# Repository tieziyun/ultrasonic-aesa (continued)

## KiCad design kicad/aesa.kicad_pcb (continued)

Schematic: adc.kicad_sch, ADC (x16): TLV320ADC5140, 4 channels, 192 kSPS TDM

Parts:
C1, C2, C3, C4, C5, C6, C7, C8, C10, C12, C14, C16: 100n 16V X7R; C_0603_1608Metric; LCSC C14663
C9, C17: 1u 50V X7R; C_0805_2012Metric; LCSC C28323
C11, C13, C15: 10u 16V X5R; C_0805_2012Metric; LCSC C15850
R1, R2, R3, R4: 2k 1%; R_0603_1608Metric; LCSC C22975
R5, R6, R7, R8: 1k 1%; R_0603_1608Metric; LCSC C21190
R9: 33 1%; R_0603_1608Metric; LCSC C23140
U1: TLV320ADC5140; Texas_RTW_WQFN-24-1EP_4x4mm_P0.5mm_EP2.7x2.7mm_ThermalVias; LCSC C2876368

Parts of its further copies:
C7101, C7102, C7103, C7104, C7105, C7106, C7107, C7108, C7110, C7112, C7114, C7116, C7201, C7202, C7203, C7204, C7205, C7206, C7207, C7208, C7210, C7212, C7214, C7216, C7301, C7302, C7303, C7304, C7305, C7306, C7307, C7308, C7310, C7312, C7314, C7316, C7401, C7402, C7403, C7404, C7405, C7406, C7407, C7408, C7410, C7412, C7414, C7416, C7501, C7502, C7503, C7504, C7505, C7506, C7507, C7508, C7510, C7512, C7514, C7516, C7601, C7602, C7603, C7604, C7605, C7606, C7607, C7608, C7610, C7612, C7614, C7616, C7701, C7702, C7703, C7704, C7705, C7706, C7707, C7708, C7710, C7712, C7714, C7716, C7801, C7802, C7803, C7804, C7805, C7806, C7807, C7808, C7810, C7812, C7814, C7816, C7901, C7902, C7903, C7904, C7905, C7906, C7907, C7908, C7910, C7912, C7914, C7916, C8001, C8002, C8003, C8004, C8005, C8006, C8007, C8008, C8010, C8012, C8014, C8016, C8101, C8102, C8103, C8104, C8105, C8106, C8107, C8108, C8110, C8112, C8114, C8116, C8201, C8202, C8203, C8204, C8205, C8206, C8207, C8208, C8210, C8212, C8214, C8216, C8301, C8302, C8303, C8304, C8305, C8306, C8307, C8308, C8310, C8312, C8314, C8316, C8401, C8402, C8403, C8404, C8405, C8406, C8407, C8408, C8410, C8412, C8414, C8416, C8501, C8502, C8503, C8504, C8505, C8506, C8507, C8508, C8510, C8512, C8514, C8516, C8601, C8602, C8603, C8604, C8605, C8606, C8607, C8608, C8610, C8612, C8614, C8616: 100n 16V X7R; C_0603_1608Metric; LCSC C14663
C7109, C7117, C7209, C7217, C7309, C7317, C7409, C7417, C7509, C7517, C7609, C7617, C7709, C7717, C7809, C7817, C7909, C7917, C8009, C8017, C8109, C8117, C8209, C8217, C8309, C8317, C8409, C8417, C8509, C8517, C8609, C8617: 1u 50V X7R; C_0805_2012Metric; LCSC C28323
C7111, C7113, C7115, C7211, C7213, C7215, C7311, C7313, C7315, C7411, C7413, C7415, C7511, C7513, C7515, C7611, C7613, C7615, C7711, C7713, C7715, C7811, C7813, C7815, C7911, C7913, C7915, C8011, C8013, C8015, C8111, C8113, C8115, C8211, C8213, C8215, C8311, C8313, C8315, C8411, C8413, C8415, C8511, C8513, C8515, C8611, C8613, C8615: 10u 16V X5R; C_0805_2012Metric; LCSC C15850
R7101, R7102, R7103, R7104, R7201, R7202, R7203, R7204, R7301, R7302, R7303, R7304, R7401, R7402, R7403, R7404, R7501, R7502, R7503, R7504, R7601, R7602, R7603, R7604, R7701, R7702, R7703, R7704, R7801, R7802, R7803, R7804, R7901, R7902, R7903, R7904, R8001, R8002, R8003, R8004, R8101, R8102, R8103, R8104, R8201, R8202, R8203, R8204, R8301, R8302, R8303, R8304, R8401, R8402, R8403, R8404, R8501, R8502, R8503, R8504, R8601, R8602, R8603, R8604: 2k 1%; R_0603_1608Metric; LCSC C22975
R7105, R7106, R7107, R7108, R7205, R7206, R7207, R7208, R7305, R7306, R7307, R7308, R7405, R7406, R7407, R7408, R7505, R7506, R7507, R7508, R7605, R7606, R7607, R7608, R7705, R7706, R7707, R7708, R7805, R7806, R7807, R7808, R7905, R7906, R7907, R7908, R8005, R8006, R8007, R8008, R8105, R8106, R8107, R8108, R8205, R8206, R8207, R8208, R8305, R8306, R8307, R8308, R8405, R8406, R8407, R8408, R8505, R8506, R8507, R8508, R8605, R8606, R8607, R8608: 1k 1%; R_0603_1608Metric; LCSC C21190
R7109, R7209, R7309, R7409, R7509, R7609, R7709, R7809, R7909, R8009, R8109, R8209, R8309, R8409, R8509, R8609: 33 1%; R_0603_1608Metric; LCSC C23140
U7101, U7201, U7301, U7401, U7501, U7601, U7701, U7801, U7901, U8001, U8101, U8201, U8301, U8401, U8501, U8601: TLV320ADC5140; Texas_RTW_WQFN-24-1EP_4x4mm_P0.5mm_EP2.7x2.7mm_ThermalVias; LCSC C2876368

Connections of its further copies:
+3V3: C7115.1, C7116.1, C7215.1, C7216.1, C7315.1, C7316.1, C7415.1, C7416.1, C7515.1, C7516.1, C7615.1, C7616.1, C7715.1, C7716.1, C7815.1, C7816.1, C7915.1, C7916.1, C8015.1, C8016.1, C8115.1, C8116.1, C8215.1, C8216.1, C8315.1, C8316.1, C8415.1, C8416.1, C8515.1, C8516.1, C8615.1, C8616.1, U7101.19 (IOVDD), U7201.16 (ADDR0_SCLK), U7201.19 (IOVDD), U7301.15 (ADDR1_MISO), U7301.19 (IOVDD), U7401.15 (ADDR1_MISO), U7401.16 (ADDR0_SCLK), U7401.19 (IOVDD), U7501.19 (IOVDD), U7601.16 (ADDR0_SCLK), U7601.19 (IOVDD), U7701.15 (ADDR1_MISO), U7701.19 (IOVDD), U7801.15 (ADDR1_MISO), U7801.16 (ADDR0_SCLK), U7801.19 (IOVDD), U7901.19 (IOVDD), U8001.16 (ADDR0_SCLK), U8001.19 (IOVDD), U8101.15 (ADDR1_MISO), U8101.19 (IOVDD), U8201.15 (ADDR1_MISO), U8201.16 (ADDR0_SCLK), U8201.19 (IOVDD), U8301.19 (IOVDD), U8401.16 (ADDR0_SCLK), U8401.19 (IOVDD), U8501.15 (ADDR1_MISO), U8501.19 (IOVDD), U8601.15 (ADDR1_MISO), U8601.16 (ADDR0_SCLK), U8601.19 (IOVDD); also elsewhere on the board
+3V3A: C7109.1, C7110.1, C7209.1, C7210.1, C7309.1, C7310.1, C7409.1, C7410.1, C7509.1, C7510.1, C7609.1, C7610.1, C7709.1, C7710.1, C7809.1, C7810.1, C7909.1, C7910.1, C8009.1, C8010.1, C8109.1, C8110.1, C8209.1, C8210.1, C8309.1, C8310.1, C8409.1, C8410.1, C8509.1, C8510.1, C8609.1, C8610.1, U7101.1 (AVDD), U7201.1 (AVDD), U7301.1 (AVDD), U7401.1 (AVDD), U7501.1 (AVDD), U7601.1 (AVDD), U7701.1 (AVDD), U7801.1 (AVDD), U7901.1 (AVDD), U8001.1 (AVDD), U8101.1 (AVDD), U8201.1 (AVDD), U8301.1 (AVDD), U8401.1 (AVDD), U8501.1 (AVDD), U8601.1 (AVDD); also elsewhere on the board
/ADCs/ADC01/AREG: C7111.1, C7112.1, U7101.2 (AREG)
/ADCs/ADC01/DREG: C7113.1, C7114.1, U7101.24 (DREG)
/ADCs/ADC01/INM1: C7105.1, U7101.7 (IN1M_GPO1)
/ADCs/ADC01/INM2: C7106.1, U7101.9 (IN2M_GPO2)
/ADCs/ADC01/INM3: C7107.1, U7101.11 (IN3M_GPO3)
/ADCs/ADC01/INM4: C7108.1, U7101.13 (IN4M_GPO4)
/ADCs/ADC01/INP1: C7101.2, U7101.6 (IN1P_GPI1)
/ADCs/ADC01/INP2: C7102.2, U7101.8 (IN2P_GPI2)
/ADCs/ADC01/INP3: C7103.2, U7101.10 (IN3P_GPI3)
/ADCs/ADC01/INP4: C7104.2, U7101.12 (IN4P_GPI4)
/ADCs/ADC01/VREF: C7117.1, U7101.3 (VREF)
/ADCs/ADC02/AREG: C7211.1, C7212.1, U7201.2 (AREG)
/ADCs/ADC02/DREG: C7213.1, C7214.1, U7201.24 (DREG)
/ADCs/ADC02/INM1: C7205.1, U7201.7 (IN1M_GPO1)
/ADCs/ADC02/INM2: C7206.1, U7201.9 (IN2M_GPO2)
/ADCs/ADC02/INM3: C7207.1, U7201.11 (IN3M_GPO3)
/ADCs/ADC02/INM4: C7208.1, U7201.13 (IN4M_GPO4)
/ADCs/ADC02/INP1: C7201.2, U7201.6 (IN1P_GPI1)
/ADCs/ADC02/INP2: C7202.2, U7201.8 (IN2P_GPI2)
/ADCs/ADC02/INP3: C7203.2, U7201.10 (IN3P_GPI3)
/ADCs/ADC02/INP4: C7204.2, U7201.12 (IN4P_GPI4)
/ADCs/ADC02/VREF: C7217.1, U7201.3 (VREF)
/ADCs/ADC03/AREG: C7311.1, C7312.1, U7301.2 (AREG)
/ADCs/ADC03/DREG: C7313.1, C7314.1, U7301.24 (DREG)
/ADCs/ADC03/INM1: C7305.1, U7301.7 (IN1M_GPO1)
/ADCs/ADC03/INM2: C7306.1, U7301.9 (IN2M_GPO2)
/ADCs/ADC03/INM3: C7307.1, U7301.11 (IN3M_GPO3)
/ADCs/ADC03/INM4: C7308.1, U7301.13 (IN4M_GPO4)
/ADCs/ADC03/INP1: C7301.2, U7301.6 (IN1P_GPI1)
/ADCs/ADC03/INP2: C7302.2, U7301.8 (IN2P_GPI2)
/ADCs/ADC03/INP3: C7303.2, U7301.10 (IN3P_GPI3)
/ADCs/ADC03/INP4: C7304.2, U7301.12 (IN4P_GPI4)
/ADCs/ADC03/VREF: C7317.1, U7301.3 (VREF)
/ADCs/ADC04/AREG: C7411.1, C7412.1, U7401.2 (AREG)
/ADCs/ADC04/DREG: C7413.1, C7414.1, U7401.24 (DREG)
/ADCs/ADC04/INM1: C7405.1, U7401.7 (IN1M_GPO1)
/ADCs/ADC04/INM2: C7406.1, U7401.9 (IN2M_GPO2)
/ADCs/ADC04/INM3: C7407.1, U7401.11 (IN3M_GPO3)
/ADCs/ADC04/INM4: C7408.1, U7401.13 (IN4M_GPO4)
/ADCs/ADC04/INP1: C7401.2, U7401.6 (IN1P_GPI1)
/ADCs/ADC04/INP2: C7402.2, U7401.8 (IN2P_GPI2)
/ADCs/ADC04/INP3: C7403.2, U7401.10 (IN3P_GPI3)
/ADCs/ADC04/INP4: C7404.2, U7401.12 (IN4P_GPI4)
/ADCs/ADC04/VREF: C7417.1, U7401.3 (VREF)
/ADCs/ADC05/AREG: C7511.1, C7512.1, U7501.2 (AREG)
/ADCs/ADC05/DREG: C7513.1, C7514.1, U7501.24 (DREG)
/ADCs/ADC05/INM1: C7505.1, U7501.7 (IN1M_GPO1)
/ADCs/ADC05/INM2: C7506.1, U7501.9 (IN2M_GPO2)
/ADCs/ADC05/INM3: C7507.1, U7501.11 (IN3M_GPO3)
/ADCs/ADC05/INM4: C7508.1, U7501.13 (IN4M_GPO4)
/ADCs/ADC05/INP1: C7501.2, U7501.6 (IN1P_GPI1)
/ADCs/ADC05/INP2: C7502.2, U7501.8 (IN2P_GPI2)
/ADCs/ADC05/INP3: C7503.2, U7501.10 (IN3P_GPI3)
/ADCs/ADC05/INP4: C7504.2, U7501.12 (IN4P_GPI4)
/ADCs/ADC05/VREF: C7517.1, U7501.3 (VREF)
/ADCs/ADC06/AREG: C7611.1, C7612.1, U7601.2 (AREG)
/ADCs/ADC06/DREG: C7613.1, C7614.1, U7601.24 (DREG)
/ADCs/ADC06/INM1: C7605.1, U7601.7 (IN1M_GPO1)
/ADCs/ADC06/INM2: C7606.1, U7601.9 (IN2M_GPO2)
/ADCs/ADC06/INM3: C7607.1, U7601.11 (IN3M_GPO3)
/ADCs/ADC06/INM4: C7608.1, U7601.13 (IN4M_GPO4)
/ADCs/ADC06/INP1: C7601.2, U7601.6 (IN1P_GPI1)
/ADCs/ADC06/INP2: C7602.2, U7601.8 (IN2P_GPI2)
/ADCs/ADC06/INP3: C7603.2, U7601.10 (IN3P_GPI3)
/ADCs/ADC06/INP4: C7604.2, U7601.12 (IN4P_GPI4)
/ADCs/ADC06/VREF: C7617.1, U7601.3 (VREF)
/ADCs/ADC07/AREG: C7711.1, C7712.1, U7701.2 (AREG)
/ADCs/ADC07/DREG: C7713.1, C7714.1, U7701.24 (DREG)
/ADCs/ADC07/INM1: C7705.1, U7701.7 (IN1M_GPO1)
/ADCs/ADC07/INM2: C7706.1, U7701.9 (IN2M_GPO2)
/ADCs/ADC07/INM3: C7707.1, U7701.11 (IN3M_GPO3)
/ADCs/ADC07/INM4: C7708.1, U7701.13 (IN4M_GPO4)
/ADCs/ADC07/INP1: C7701.2, U7701.6 (IN1P_GPI1)
/ADCs/ADC07/INP2: C7702.2, U7701.8 (IN2P_GPI2)
/ADCs/ADC07/INP3: C7703.2, U7701.10 (IN3P_GPI3)
/ADCs/ADC07/INP4: C7704.2, U7701.12 (IN4P_GPI4)
/ADCs/ADC07/VREF: C7717.1, U7701.3 (VREF)
/ADCs/ADC08/AREG: C7811.1, C7812.1, U7801.2 (AREG)
/ADCs/ADC08/DREG: C7813.1, C7814.1, U7801.24 (DREG)
/ADCs/ADC08/INM1: C7805.1, U7801.7 (IN1M_GPO1)
/ADCs/ADC08/INM2: C7806.1, U7801.9 (IN2M_GPO2)
/ADCs/ADC08/INM3: C7807.1, U7801.11 (IN3M_GPO3)
/ADCs/ADC08/INM4: C7808.1, U7801.13 (IN4M_GPO4)
/ADCs/ADC08/INP1: C7801.2, U7801.6 (IN1P_GPI1)
/ADCs/ADC08/INP2: C7802.2, U7801.8 (IN2P_GPI2)
/ADCs/ADC08/INP3: C7803.2, U7801.10 (IN3P_GPI3)
/ADCs/ADC08/INP4: C7804.2, U7801.12 (IN4P_GPI4)
/ADCs/ADC08/VREF: C7817.1, U7801.3 (VREF)
/ADCs/ADC09/AREG: C7911.1, C7912.1, U7901.2 (AREG)
/ADCs/ADC09/DREG: C7913.1, C7914.1, U7901.24 (DREG)
/ADCs/ADC09/INM1: C7905.1, U7901.7 (IN1M_GPO1)
/ADCs/ADC09/INM2: C7906.1, U7901.9 (IN2M_GPO2)
/ADCs/ADC09/INM3: C7907.1, U7901.11 (IN3M_GPO3)
/ADCs/ADC09/INM4: C7908.1, U7901.13 (IN4M_GPO4)
/ADCs/ADC09/INP1: C7901.2, U7901.6 (IN1P_GPI1)
/ADCs/ADC09/INP2: C7902.2, U7901.8 (IN2P_GPI2)
/ADCs/ADC09/INP3: C7903.2, U7901.10 (IN3P_GPI3)
/ADCs/ADC09/INP4: C7904.2, U7901.12 (IN4P_GPI4)
/ADCs/ADC09/VREF: C7917.1, U7901.3 (VREF)
/ADCs/ADC10/AREG: C8011.1, C8012.1, U8001.2 (AREG)
/ADCs/ADC10/DREG: C8013.1, C8014.1, U8001.24 (DREG)
/ADCs/ADC10/INM1: C8005.1, U8001.7 (IN1M_GPO1)
/ADCs/ADC10/INM2: C8006.1, U8001.9 (IN2M_GPO2)
/ADCs/ADC10/INM3: C8007.1, U8001.11 (IN3M_GPO3)
/ADCs/ADC10/INM4: C8008.1, U8001.13 (IN4M_GPO4)
/ADCs/ADC10/INP1: C8001.2, U8001.6 (IN1P_GPI1)
/ADCs/ADC10/INP2: C8002.2, U8001.8 (IN2P_GPI2)
/ADCs/ADC10/INP3: C8003.2, U8001.10 (IN3P_GPI3)
/ADCs/ADC10/INP4: C8004.2, U8001.12 (IN4P_GPI4)
/ADCs/ADC10/VREF: C8017.1, U8001.3 (VREF)
/ADCs/ADC11/AREG: C8111.1, C8112.1, U8101.2 (AREG)
/ADCs/ADC11/DREG: C8113.1, C8114.1, U8101.24 (DREG)
/ADCs/ADC11/INM1: C8105.1, U8101.7 (IN1M_GPO1)
/ADCs/ADC11/INM2: C8106.1, U8101.9 (IN2M_GPO2)
/ADCs/ADC11/INM3: C8107.1, U8101.11 (IN3M_GPO3)
/ADCs/ADC11/INM4: C8108.1, U8101.13 (IN4M_GPO4)
/ADCs/ADC11/INP1: C8101.2, U8101.6 (IN1P_GPI1)
/ADCs/ADC11/INP2: C8102.2, U8101.8 (IN2P_GPI2)
/ADCs/ADC11/INP3: C8103.2, U8101.10 (IN3P_GPI3)
/ADCs/ADC11/INP4: C8104.2, U8101.12 (IN4P_GPI4)
/ADCs/ADC11/VREF: C8117.1, U8101.3 (VREF)
/ADCs/ADC12/AREG: C8211.1, C8212.1, U8201.2 (AREG)
/ADCs/ADC12/DREG: C8213.1, C8214.1, U8201.24 (DREG)
/ADCs/ADC12/INM1: C8205.1, U8201.7 (IN1M_GPO1)
/ADCs/ADC12/INM2: C8206.1, U8201.9 (IN2M_GPO2)
/ADCs/ADC12/INM3: C8207.1, U8201.11 (IN3M_GPO3)
/ADCs/ADC12/INM4: C8208.1, U8201.13 (IN4M_GPO4)
/ADCs/ADC12/INP1: C8201.2, U8201.6 (IN1P_GPI1)
/ADCs/ADC12/INP2: C8202.2, U8201.8 (IN2P_GPI2)
/ADCs/ADC12/INP3: C8203.2, U8201.10 (IN3P_GPI3)
/ADCs/ADC12/INP4: C8204.2, U8201.12 (IN4P_GPI4)
/ADCs/ADC12/VREF: C8217.1, U8201.3 (VREF)
/ADCs/ADC13/AREG: C8311.1, C8312.1, U8301.2 (AREG)
/ADCs/ADC13/DREG: C8313.1, C8314.1, U8301.24 (DREG)
/ADCs/ADC13/INM1: C8305.1, U8301.7 (IN1M_GPO1)
/ADCs/ADC13/INM2: C8306.1, U8301.9 (IN2M_GPO2)
/ADCs/ADC13/INM3: C8307.1, U8301.11 (IN3M_GPO3)
/ADCs/ADC13/INM4: C8308.1, U8301.13 (IN4M_GPO4)
/ADCs/ADC13/INP1: C8301.2, U8301.6 (IN1P_GPI1)
/ADCs/ADC13/INP2: C8302.2, U8301.8 (IN2P_GPI2)
/ADCs/ADC13/INP3: C8303.2, U8301.10 (IN3P_GPI3)
/ADCs/ADC13/INP4: C8304.2, U8301.12 (IN4P_GPI4)
/ADCs/ADC13/VREF: C8317.1, U8301.3 (VREF)
/ADCs/ADC14/AREG: C8411.1, C8412.1, U8401.2 (AREG)
/ADCs/ADC14/DREG: C8413.1, C8414.1, U8401.24 (DREG)
/ADCs/ADC14/INM1: C8405.1, U8401.7 (IN1M_GPO1)
/ADCs/ADC14/INM2: C8406.1, U8401.9 (IN2M_GPO2)
/ADCs/ADC14/INM3: C8407.1, U8401.11 (IN3M_GPO3)
/ADCs/ADC14/INM4: C8408.1, U8401.13 (IN4M_GPO4)
/ADCs/ADC14/INP1: C8401.2, U8401.6 (IN1P_GPI1)
/ADCs/ADC14/INP2: C8402.2, U8401.8 (IN2P_GPI2)
/ADCs/ADC14/INP3: C8403.2, U8401.10 (IN3P_GPI3)
/ADCs/ADC14/INP4: C8404.2, U8401.12 (IN4P_GPI4)
/ADCs/ADC14/VREF: C8417.1, U8401.3 (VREF)
/ADCs/ADC15/AREG: C8511.1, C8512.1, U8501.2 (AREG)
/ADCs/ADC15/DREG: C8513.1, C8514.1, U8501.24 (DREG)
/ADCs/ADC15/INM1: C8505.1, U8501.7 (IN1M_GPO1)
/ADCs/ADC15/INM2: C8506.1, U8501.9 (IN2M_GPO2)
/ADCs/ADC15/INM3: C8507.1, U8501.11 (IN3M_GPO3)
/ADCs/ADC15/INM4: C8508.1, U8501.13 (IN4M_GPO4)
/ADCs/ADC15/INP1: C8501.2, U8501.6 (IN1P_GPI1)
/ADCs/ADC15/INP2: C8502.2, U8501.8 (IN2P_GPI2)
/ADCs/ADC15/INP3: C8503.2, U8501.10 (IN3P_GPI3)
/ADCs/ADC15/INP4: C8504.2, U8501.12 (IN4P_GPI4)
/ADCs/ADC15/VREF: C8517.1, U8501.3 (VREF)
/ADCs/ADC16/AREG: C8611.1, C8612.1, U8601.2 (AREG)
/ADCs/ADC16/DREG: C8613.1, C8614.1, U8601.24 (DREG)
/ADCs/ADC16/INM1: C8605.1, U8601.7 (IN1M_GPO1)
/ADCs/ADC16/INM2: C8606.1, U8601.9 (IN2M_GPO2)
/ADCs/ADC16/INM3: C8607.1, U8601.11 (IN3M_GPO3)
/ADCs/ADC16/INM4: C8608.1, U8601.13 (IN4M_GPO4)
/ADCs/ADC16/INP1: C8601.2, U8601.6 (IN1P_GPI1)
/ADCs/ADC16/INP2: C8602.2, U8601.8 (IN2P_GPI2)
/ADCs/ADC16/INP3: C8603.2, U8601.10 (IN3P_GPI3)
/ADCs/ADC16/INP4: C8604.2, U8601.12 (IN4P_GPI4)
/ADCs/ADC16/VREF: C8617.1, U8601.3 (VREF)
ADC_BCLK_A: U7101.22 (BCLK), U7201.22 (BCLK), U7301.22 (BCLK), U7401.22 (BCLK); also elsewhere on the board
ADC_BCLK_B: U7501.22 (BCLK), U7601.22 (BCLK), U7701.22 (BCLK), U7801.22 (BCLK); also elsewhere on the board
ADC_BCLK_C: U7901.22 (BCLK), U8001.22 (BCLK), U8101.22 (BCLK), U8201.22 (BCLK); also elsewhere on the board
ADC_BCLK_D: U8301.22 (BCLK), U8401.22 (BCLK), U8501.22 (BCLK), U8601.22 (BCLK); also elsewhere on the board
ADC_FSYNC_A: U7101.23 (FSYNC), U7201.23 (FSYNC), U7301.23 (FSYNC), U7401.23 (FSYNC); also elsewhere on the board
ADC_FSYNC_B: U7501.23 (FSYNC), U7601.23 (FSYNC), U7701.23 (FSYNC), U7801.23 (FSYNC); also elsewhere on the board
ADC_FSYNC_C: U7901.23 (FSYNC), U8001.23 (FSYNC), U8101.23 (FSYNC), U8201.23 (FSYNC); also elsewhere on the board
ADC_FSYNC_D: U8301.23 (FSYNC), U8401.23 (FSYNC), U8501.23 (FSYNC), U8601.23 (FSYNC); also elsewhere on the board
ADC_SCL: U7101.17 (SCL_MOSI), U7201.17 (SCL_MOSI), U7301.17 (SCL_MOSI), U7401.17 (SCL_MOSI), U7501.17 (SCL_MOSI), U7601.17 (SCL_MOSI), U7701.17 (SCL_MOSI), U7801.17 (SCL_MOSI), U7901.17 (SCL_MOSI), U8001.17 (SCL_MOSI), U8101.17 (SCL_MOSI), U8201.17 (SCL_MOSI), U8301.17 (SCL_MOSI), U8401.17 (SCL_MOSI), U8501.17 (SCL_MOSI), U8601.17 (SCL_MOSI); also elsewhere on the board
ADC_SDA1: U7101.18 (SDA_SSZ), U7201.18 (SDA_SSZ), U7301.18 (SDA_SSZ), U7401.18 (SDA_SSZ); also elsewhere on the board
ADC_SDA2: U7501.18 (SDA_SSZ), U7601.18 (SDA_SSZ), U7701.18 (SDA_SSZ), U7801.18 (SDA_SSZ); also elsewhere on the board
ADC_SDA3: U7901.18 (SDA_SSZ), U8001.18 (SDA_SSZ), U8101.18 (SDA_SSZ), U8201.18 (SDA_SSZ); also elsewhere on the board
ADC_SDA4: U8301.18 (SDA_SSZ), U8401.18 (SDA_SSZ), U8501.18 (SDA_SSZ), U8601.18 (SDA_SSZ); also elsewhere on the board
ADC_SDOUT1: R7109.2; also elsewhere on the board
ADC_SDOUT2: R7209.2; also elsewhere on the board
ADC_SDOUT3: R7309.2; also elsewhere on the board
ADC_SDOUT4: R7409.2; also elsewhere on the board
ADC_SDOUT5: R7509.2; also elsewhere on the board
ADC_SDOUT6: R7609.2; also elsewhere on the board
ADC_SDOUT7: R7709.2; also elsewhere on the board
ADC_SDOUT8: R7809.2; also elsewhere on the board
ADC_SDOUT9: R7909.2; also elsewhere on the board
ADC_SDOUT10: R8009.2; also elsewhere on the board
ADC_SDOUT11: R8109.2; also elsewhere on the board
ADC_SDOUT12: R8209.2; also elsewhere on the board
ADC_SDOUT13: R8309.2; also elsewhere on the board
ADC_SDOUT14: R8409.2; also elsewhere on the board
ADC_SDOUT15: R8509.2; also elsewhere on the board
ADC_SDOUT16: R8609.2; also elsewhere on the board
ADC_SHDNZ: U7101.14 (SHDNZ), U7201.14 (SHDNZ), U7301.14 (SHDNZ), U7401.14 (SHDNZ), U7501.14 (SHDNZ), U7601.14 (SHDNZ), U7701.14 (SHDNZ), U7801.14 (SHDNZ), U7901.14 (SHDNZ), U8001.14 (SHDNZ), U8101.14 (SHDNZ), U8201.14 (SHDNZ), U8301.14 (SHDNZ), U8401.14 (SHDNZ), U8501.14 (SHDNZ), U8601.14 (SHDNZ); also elsewhere on the board
GND: C7105.2, C7106.2, C7107.2, C7108.2, C7109.2, C7110.2, C7111.2, C7112.2, C7113.2, C7114.2, C7115.2, C7116.2, C7117.2, C7205.2, C7206.2, C7207.2, C7208.2, C7209.2, C7210.2, C7211.2, C7212.2, C7213.2, C7214.2, C7215.2, C7216.2, C7217.2, C7305.2, C7306.2, C7307.2, C7308.2, C7309.2, C7310.2, C7311.2, C7312.2, C7313.2, C7314.2, C7315.2, C7316.2, C7317.2, C7405.2, C7406.2, C7407.2, C7408.2, C7409.2, C7410.2, C7411.2, C7412.2, C7413.2, C7414.2, C7415.2, C7416.2, C7417.2, C7505.2, C7506.2, C7507.2, C7508.2, C7509.2, C7510.2, C7511.2, C7512.2, C7513.2, C7514.2, C7515.2, C7516.2, C7517.2, C7605.2, C7606.2, C7607.2, C7608.2, C7609.2, C7610.2, C7611.2, C7612.2, C7613.2, C7614.2, C7615.2, C7616.2, C7617.2, C7705.2, C7706.2, C7707.2, C7708.2, C7709.2, C7710.2, C7711.2, C7712.2, C7713.2, C7714.2, C7715.2, C7716.2, C7717.2, C7805.2, C7806.2, C7807.2, C7808.2, C7809.2, C7810.2, C7811.2, C7812.2, C7813.2, C7814.2, C7815.2, C7816.2, C7817.2, C7905.2, C7906.2, C7907.2, C7908.2, C7909.2, C7910.2, C7911.2, C7912.2, C7913.2, C7914.2, C7915.2, C7916.2, C7917.2, C8005.2, C8006.2, C8007.2, C8008.2, C8009.2, C8010.2, C8011.2, C8012.2, C8013.2, C8014.2, C8015.2, C8016.2, C8017.2, C8105.2, C8106.2, C8107.2, C8108.2, C8109.2, C8110.2, C8111.2, C8112.2, C8113.2, C8114.2, C8115.2, C8116.2, C8117.2, C8205.2, C8206.2, C8207.2, C8208.2, C8209.2, C8210.2, C8211.2, C8212.2, C8213.2, C8214.2, C8215.2, C8216.2, C8217.2, C8305.2, C8306.2, C8307.2, C8308.2, C8309.2, C8310.2, C8311.2, C8312.2, C8313.2, C8314.2, C8315.2, C8316.2, C8317.2, C8405.2, C8406.2, C8407.2, C8408.2, C8409.2, C8410.2, C8411.2, C8412.2, C8413.2, C8414.2, C8415.2, C8416.2, C8417.2, C8505.2, C8506.2, C8507.2, C8508.2, C8509.2, C8510.2, C8511.2, C8512.2, C8513.2, C8514.2, C8515.2, C8516.2, C8517.2, C8605.2, C8606.2, C8607.2, C8608.2, C8609.2, C8610.2, C8611.2, C8612.2, C8613.2, C8614.2, C8615.2, C8616.2, C8617.2, R7105.2, R7106.2, R7107.2, R7108.2, R7205.2, R7206.2, R7207.2, R7208.2, R7305.2, R7306.2, R7307.2, R7308.2, R7405.2, R7406.2, R7407.2, R7408.2, R7505.2, R7506.2, R7507.2, R7508.2, R7605.2, R7606.2, R7607.2, R7608.2, R7705.2, R7706.2, R7707.2, R7708.2, R7805.2, R7806.2, R7807.2, R7808.2, R7905.2, R7906.2, R7907.2, R7908.2, R8005.2, R8006.2, R8007.2, R8008.2, R8105.2, R8106.2, R8107.2, R8108.2, R8205.2, R8206.2, R8207.2, R8208.2, R8305.2, R8306.2, R8307.2, R8308.2, R8405.2, R8406.2, R8407.2, R8408.2, R8505.2, R8506.2, R8507.2, R8508.2, R8605.2, R8606.2, R8607.2, R8608.2, U7101.4 (AVSS), U7101.15 (ADDR1_MISO), U7101.16 (ADDR0_SCLK), U7101.25 (VSS), U7201.4 (AVSS), U7201.15 (ADDR1_MISO), U7201.25 (VSS), U7301.4 (AVSS), U7301.16 (ADDR0_SCLK), U7301.25 (VSS), U7401.4 (AVSS), U7401.25 (VSS), U7501.4 (AVSS), U7501.15 (ADDR1_MISO), U7501.16 (ADDR0_SCLK), U7501.25 (VSS), U7601.4 (AVSS), U7601.15 (ADDR1_MISO), U7601.25 (VSS), U7701.4 (AVSS), U7701.16 (ADDR0_SCLK), U7701.25 (VSS), U7801.4 (AVSS), U7801.25 (VSS), U7901.4 (AVSS), U7901.15 (ADDR1_MISO), U7901.16 (ADDR0_SCLK), U7901.25 (VSS), U8001.4 (AVSS), U8001.15 (ADDR1_MISO), U8001.25 (VSS), U8101.4 (AVSS), U8101.16 (ADDR0_SCLK), U8101.25 (VSS), U8201.4 (AVSS), U8201.25 (VSS), U8301.4 (AVSS), U8301.15 (ADDR1_MISO), U8301.16 (ADDR0_SCLK), U8301.25 (VSS), U8401.4 (AVSS), U8401.15 (ADDR1_MISO), U8401.25 (VSS), U8501.4 (AVSS), U8501.16 (ADDR0_SCLK), U8501.25 (VSS), U8601.4 (AVSS), U8601.25 (VSS); also elsewhere on the board
unnamed: C7101.1, R7101.2, R7105.1
unnamed: C7102.1, R7102.2, R7106.1
unnamed: C7103.1, R7103.2, R7107.1
unnamed: C7104.1, R7104.2, R7108.1
unnamed: C7201.1, R7201.2, R7205.1
unnamed: C7202.1, R7202.2, R7206.1
unnamed: C7203.1, R7203.2, R7207.1
unnamed: C7204.1, R7204.2, R7208.1
unnamed: C7301.1, R7301.2, R7305.1
unnamed: C7302.1, R7302.2, R7306.1
unnamed: C7303.1, R7303.2, R7307.1
unnamed: C7304.1, R7304.2, R7308.1
unnamed: C7401.1, R7401.2, R7405.1
unnamed: C7402.1, R7402.2, R7406.1
unnamed: C7403.1, R7403.2, R7407.1
unnamed: C7404.1, R7404.2, R7408.1
unnamed: C7501.1, R7501.2, R7505.1
unnamed: C7502.1, R7502.2, R7506.1
unnamed: C7503.1, R7503.2, R7507.1
unnamed: C7504.1, R7504.2, R7508.1
unnamed: C7601.1, R7601.2, R7605.1
unnamed: C7602.1, R7602.2, R7606.1
unnamed: C7603.1, R7603.2, R7607.1
unnamed: C7604.1, R7604.2, R7608.1
unnamed: C7701.1, R7701.2, R7705.1
unnamed: C7702.1, R7702.2, R7706.1
unnamed: C7703.1, R7703.2, R7707.1
unnamed: C7704.1, R7704.2, R7708.1
unnamed: C7801.1, R7801.2, R7805.1
unnamed: C7802.1, R7802.2, R7806.1
unnamed: C7803.1, R7803.2, R7807.1
unnamed: C7804.1, R7804.2, R7808.1
unnamed: C7901.1, R7901.2, R7905.1
unnamed: C7902.1, R7902.2, R7906.1
unnamed: C7903.1, R7903.2, R7907.1
unnamed: C7904.1, R7904.2, R7908.1
unnamed: C8001.1, R8001.2, R8005.1
unnamed: C8002.1, R8002.2, R8006.1
unnamed: C8003.1, R8003.2, R8007.1
unnamed: C8004.1, R8004.2, R8008.1
unnamed: C8101.1, R8101.2, R8105.1
unnamed: C8102.1, R8102.2, R8106.1
unnamed: C8103.1, R8103.2, R8107.1
unnamed: C8104.1, R8104.2, R8108.1
unnamed: C8201.1, R8201.2, R8205.1
unnamed: C8202.1, R8202.2, R8206.1
unnamed: C8203.1, R8203.2, R8207.1
unnamed: C8204.1, R8204.2, R8208.1
unnamed: C8301.1, R8301.2, R8305.1
unnamed: C8302.1, R8302.2, R8306.1
unnamed: C8303.1, R8303.2, R8307.1
unnamed: C8304.1, R8304.2, R8308.1
unnamed: C8401.1, R8401.2, R8405.1
unnamed: C8402.1, R8402.2, R8406.1
unnamed: C8403.1, R8403.2, R8407.1
unnamed: C8404.1, R8404.2, R8408.1
unnamed: C8501.1, R8501.2, R8505.1
unnamed: C8502.1, R8502.2, R8506.1
unnamed: C8503.1, R8503.2, R8507.1
unnamed: C8504.1, R8504.2, R8508.1
unnamed: C8601.1, R8601.2, R8605.1
unnamed: C8602.1, R8602.2, R8606.1
unnamed: C8603.1, R8603.2, R8607.1
unnamed: C8604.1, R8604.2, R8608.1
unnamed: R7109.1, U7101.21 (SDOUT)
unnamed: R7209.1, U7201.21 (SDOUT)
unnamed: R7309.1, U7301.21 (SDOUT)
unnamed: R7409.1, U7401.21 (SDOUT)
unnamed: R7509.1, U7501.21 (SDOUT)
unnamed: R7609.1, U7601.21 (SDOUT)
unnamed: R7709.1, U7701.21 (SDOUT)
unnamed: R7809.1, U7801.21 (SDOUT)
unnamed: R7909.1, U7901.21 (SDOUT)
unnamed: R8009.1, U8001.21 (SDOUT)
unnamed: R8109.1, U8101.21 (SDOUT)
unnamed: R8209.1, U8201.21 (SDOUT)
unnamed: R8309.1, U8301.21 (SDOUT)
unnamed: R8409.1, U8401.21 (SDOUT)
unnamed: R8509.1, U8501.21 (SDOUT)
unnamed: R8609.1, U8601.21 (SDOUT)
RX1: R7104.1; also elsewhere on the board
RX2: R7103.1; also elsewhere on the board
RX3: R7102.1; also elsewhere on the board
RX4: R7101.1; also elsewhere on the board
RX5: R7204.1; also elsewhere on the board
RX6: R7203.1; also elsewhere on the board
RX7: R7202.1; also elsewhere on the board
RX8: R7201.1; also elsewhere on the board
RX9: R7304.1; also elsewhere on the board
RX10: R7303.1; also elsewhere on the board
RX11: R7302.1; also elsewhere on the board
RX12: R7301.1; also elsewhere on the board
RX13: R7404.1; also elsewhere on the board
RX14: R7403.1; also elsewhere on the board
RX15: R7402.1; also elsewhere on the board
RX16: R7401.1; also elsewhere on the board
RX17: R7504.1; also elsewhere on the board
RX18: R7503.1; also elsewhere on the board
RX19: R7502.1; also elsewhere on the board
RX20: R7501.1; also elsewhere on the board
RX21: R7604.1; also elsewhere on the board
RX22: R7603.1; also elsewhere on the board
RX23: R7602.1; also elsewhere on the board
RX24: R7601.1; also elsewhere on the board
RX25: R7704.1; also elsewhere on the board
RX26: R7703.1; also elsewhere on the board
RX27: R7702.1; also elsewhere on the board
RX28: R7701.1; also elsewhere on the board
RX29: R7804.1; also elsewhere on the board
RX30: R7803.1; also elsewhere on the board
RX31: R7802.1; also elsewhere on the board
RX32: R7801.1; also elsewhere on the board
RX33: R7904.1; also elsewhere on the board
RX34: R7903.1; also elsewhere on the board
RX35: R7902.1; also elsewhere on the board
RX36: R7901.1; also elsewhere on the board
RX37: R8004.1; also elsewhere on the board
RX38: R8003.1; also elsewhere on the board
RX39: R8002.1; also elsewhere on the board
RX40: R8001.1; also elsewhere on the board
RX41: R8104.1; also elsewhere on the board
RX42: R8103.1; also elsewhere on the board
RX43: R8102.1; also elsewhere on the board
RX44: R8101.1; also elsewhere on the board
RX45: R8204.1; also elsewhere on the board
RX46: R8203.1; also elsewhere on the board
RX47: R8202.1; also elsewhere on the board
RX48: R8201.1; also elsewhere on the board
RX49: R8304.1; also elsewhere on the board
RX50: R8303.1; also elsewhere on the board
RX51: R8302.1; also elsewhere on the board
RX52: R8301.1; also elsewhere on the board
RX53: R8404.1; also elsewhere on the board
RX54: R8403.1; also elsewhere on the board
RX55: R8402.1; also elsewhere on the board
RX56: R8401.1; also elsewhere on the board
RX57: R8504.1; also elsewhere on the board
RX58: R8503.1; also elsewhere on the board
RX59: R8502.1; also elsewhere on the board
RX60: R8501.1; also elsewhere on the board
RX61: R8604.1; also elsewhere on the board
RX62: R8603.1; also elsewhere on the board
RX63: R8602.1; also elsewhere on the board
RX64: R8601.1; also elsewhere on the board

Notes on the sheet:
Input: 2k/1k divider (x0.31 with the 10 k input) keeps the receiver's +-4.2 V worst case inside the 1.41 V peak full scale; 100 nF couples to the ADC's own bias (150 Hz high-pass).
Per channel, set at boot: CHx_INSRC = single-ended (01), CHx_IMP = 10 k (01), AC-coupled, fixed 0 dB gain, DRE and AGC OFF (they change gain on the fly and break channel matching).
ADC: TLV320ADC5140 (TI, 4 channels, up to 768 kSPS). Run at 192 kSPS: flat to about 86 kHz.
TDM slave: BCLK 18.432 MHz, FSYNC 192 kHz from the FPGA (shared by all 16 ADCs, so all 64 channels sample at the same instant). 4 slots x 24 bits on SDOUT.
Decoupling at the pins (datasheet Figure 172): AVDD 1 uF + 100 nF, AREG and DREG 10 uF + 100 nF, IOVDD 10 uF + 100 nF, VREF 1 uF
I2C: SCL shared, SDA per group of 4 ADCs; A1/A0 set the address 0x4C-0x4F inside the group. Config writes can use I2C broadcast (P0_R2 I2C_BRDCAST_EN).
Also: ADC_FSCALE 2.75 V (1 Vrms single-ended full scale), AREG_SELECT = 1, TX_EDGE = 1 (the FPGA latches SDOUT one BCLK after launch).
Ports IN1-IN4 are the block's four elements in order; IN1 feeds ADC channel 4 ... IN4 channel 1 (the order the receive lanes reach the inputs on the board). TDM: channel c carries element 4k-4 + (5 - c).
Channel inputs: 2k + 1k divider, 100 nF AC coupling (single-ended, INxM AC-grounded)
Power-up: SHDNZ (ADC_SHDNZ, pulled low on the header sheet) stays low until the rails settle, then wait 2 ms before I2C.

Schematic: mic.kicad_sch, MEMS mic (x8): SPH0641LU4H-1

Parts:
C1: 100n 50V C0G 1206; C_1206_3216Metric; LCSC C170182
MK1: SPH0641LU4H-1; Knowles_LGA-5_3.5x2.65mm; LCSC C2879853
R1: 33 1%; R_0603_1608Metric; LCSC C23140

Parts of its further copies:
C14101, C14201, C14301, C14401, C14501, C14601, C14701, C14801: 100n 50V C0G 1206; C_1206_3216Metric; LCSC C170182
MK14101, MK14201, MK14301, MK14401, MK14501, MK14601, MK14701, MK14801: SPH0641LU4H-1; Knowles_LGA-5_3.5x2.65mm; LCSC C2879853
R14101, R14201, R14301, R14401, R14501, R14601, R14701, R14801: 33 1%; R_0603_1608Metric; LCSC C23140

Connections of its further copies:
3V3_MIC: C14101.1, C14201.1, C14301.1, C14401.1, C14501.1, C14601.1, C14701.1, C14801.1, MK14101.2 (SEL), MK14101.5 (VDD), MK14201.5 (VDD), MK14301.2 (SEL), MK14301.5 (VDD), MK14401.5 (VDD), MK14501.2 (SEL), MK14501.5 (VDD), MK14601.5 (VDD), MK14701.2 (SEL), MK14701.5 (VDD), MK14801.5 (VDD); also elsewhere on the board
GND: C14101.2, C14201.2, C14301.2, C14401.2, C14501.2, C14601.2, C14701.2, C14801.2, MK14101.3 (GND), MK14201.2 (SEL), MK14201.3 (GND), MK14301.3 (GND), MK14401.2 (SEL), MK14401.3 (GND), MK14501.3 (GND), MK14601.2 (SEL), MK14601.3 (GND), MK14701.3 (GND), MK14801.2 (SEL), MK14801.3 (GND); also elsewhere on the board
MIC_CLK_A: MK14101.4 (CLOCK), MK14201.4 (CLOCK); also elsewhere on the board
MIC_CLK_B: MK14301.4 (CLOCK), MK14401.4 (CLOCK); also elsewhere on the board
MIC_CLK_C: MK14501.4 (CLOCK), MK14601.4 (CLOCK); also elsewhere on the board
MIC_CLK_D: MK14701.4 (CLOCK), MK14801.4 (CLOCK); also elsewhere on the board
MIC_DATA0: R14101.2, R14201.2; also elsewhere on the board
MIC_DATA1: R14301.2, R14401.2; also elsewhere on the board
MIC_DATA2: R14501.2, R14601.2; also elsewhere on the board
MIC_DATA3: R14701.2, R14801.2; also elsewhere on the board
unnamed: MK14101.1 (DATA), R14101.1
unnamed: MK14201.1 (DATA), R14201.1
unnamed: MK14301.1 (DATA), R14301.1
unnamed: MK14401.1 (DATA), R14401.1
unnamed: MK14501.1 (DATA), R14501.1
unnamed: MK14601.1 (DATA), R14601.1
unnamed: MK14701.1 (DATA), R14701.1
unnamed: MK14801.1 (DATA), R14801.1

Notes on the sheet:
Mounted on the back, sound port through a board hole. 3V3_MIC is the ferrite-filtered rail (power sheet).
MEMS mic SPH0641LU4H-1 (PDM). Two mics share DATA: SEL high on one, low on the other.

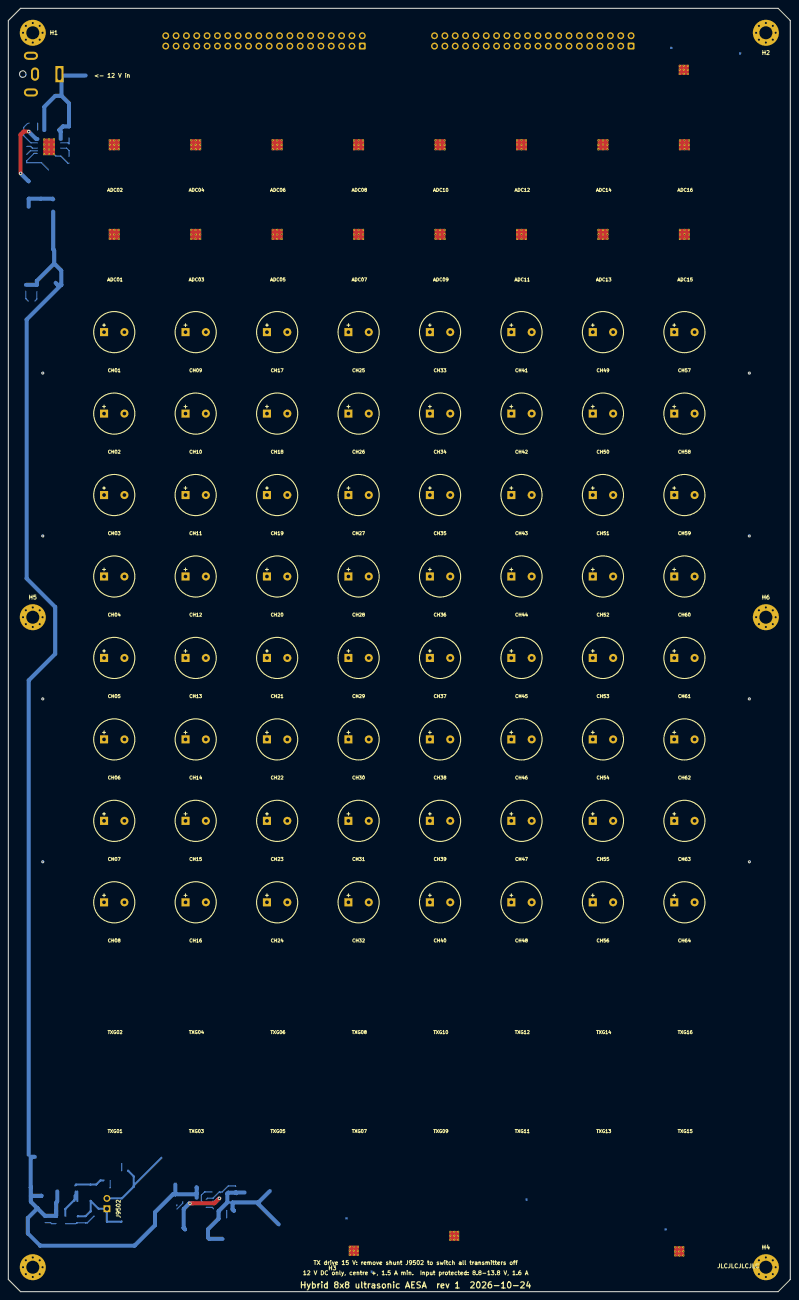
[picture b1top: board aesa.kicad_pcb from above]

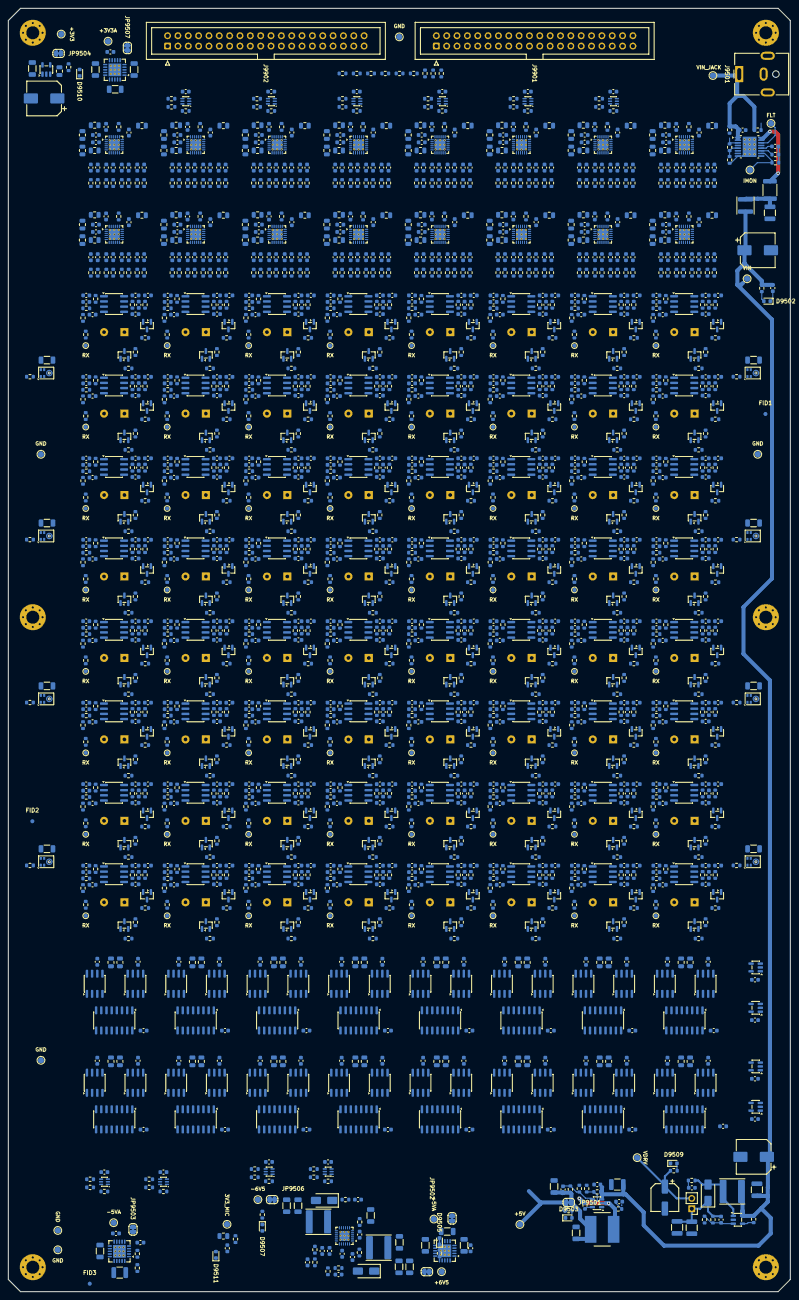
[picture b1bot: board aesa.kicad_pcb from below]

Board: 4 copper layers, 192.0 x 315.1 mm, 2139 parts (2069 on the bottom side), 1185 nets.

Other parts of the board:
FID1, FID2, FID3: Fiducial; Fiducial_1mm_Mask2mm
H1, H2, H3, H4, H5, H6: M3; MountingHole_3.2mm_M3_Pad_Via

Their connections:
GND: H1.1, H2.1, H3.1, H4.1, H5.1, H6.1; also elsewhere on the board

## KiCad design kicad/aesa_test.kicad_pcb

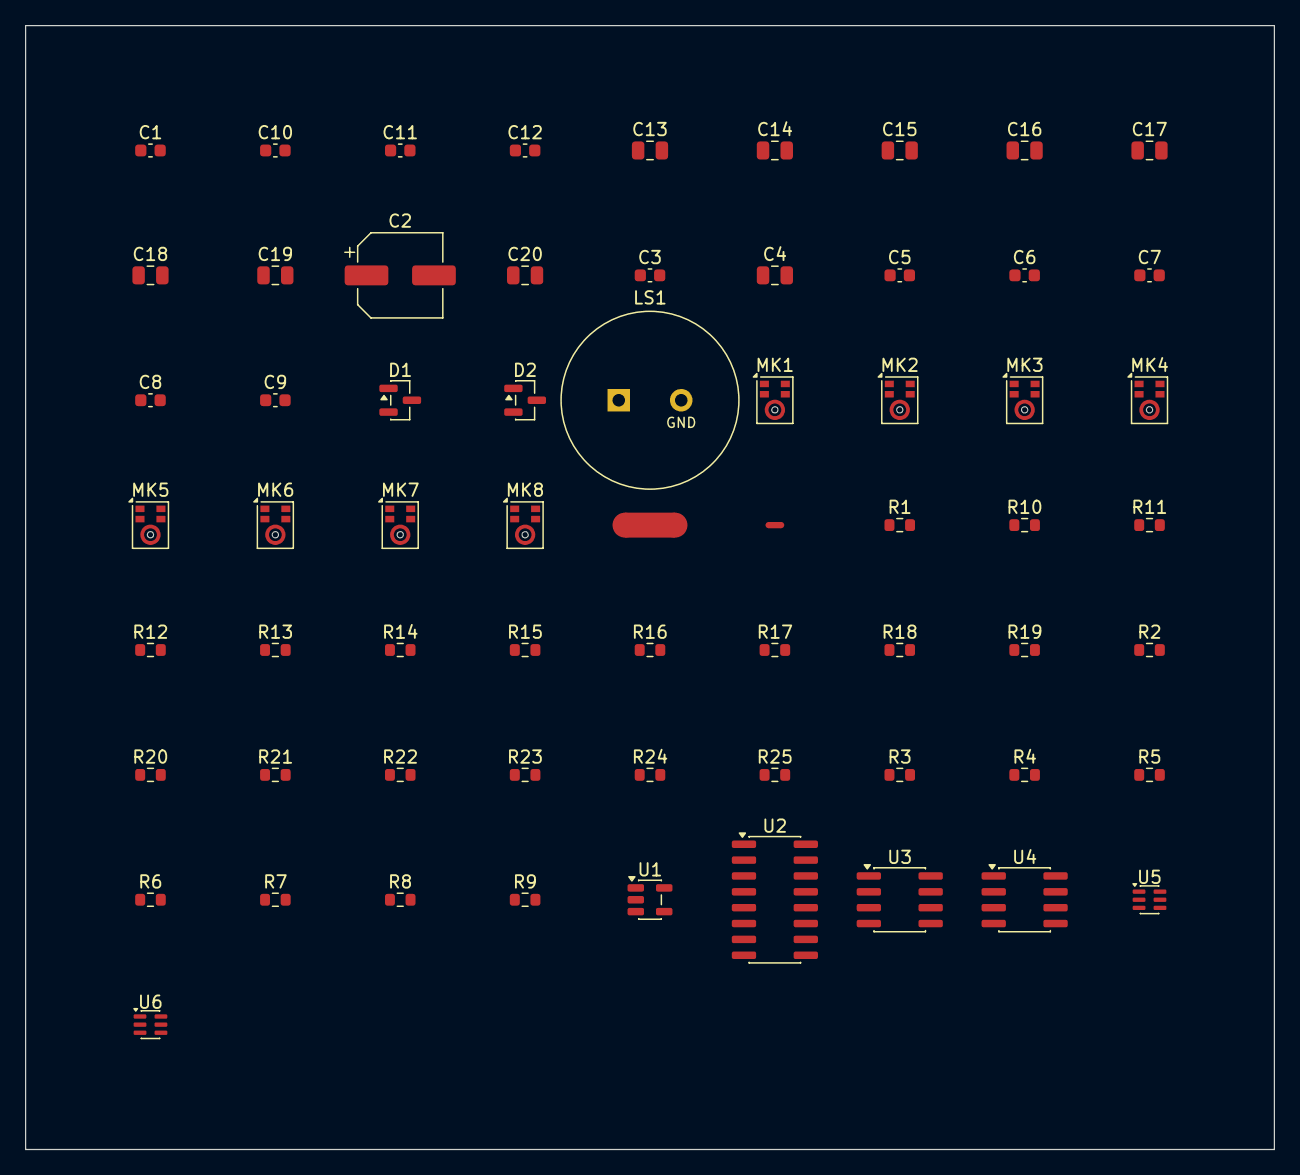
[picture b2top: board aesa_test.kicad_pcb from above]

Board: 2 copper layers, 100.0 x 90.0 mm, 64 parts (0 on the bottom side), 44 nets, no tracks yet.

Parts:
C1, C3, C6, C7, C8, C11, C12: 100n 16V X7R; C_0603_1608Metric
C2: 47u 35V; CP_Elec_6.3x7.7
C4: 1u 50V X7R; C_0805_2012Metric
C5: 100n 50V X7R; C_0603_1608Metric
C9, C10: 1n 50V C0G 1%; C_0603_1608Metric
C13, C14, C15, C16, C17, C18, C19, C20: 100n 16V C0G; C_0805_2012Metric
D1, D2: BAV99; SOT-23
LS1: CUSA-TR65-065-2200-TH68; CUSA-TR65
MK1, MK2, MK3, MK4, MK5, MK6, MK7, MK8: SPH0641LU4H-1; Knowles_LGA-5_3.5x2.65mm
NT1: NetTie AGND-PGND; NetTie-2_SMD_Pad2.0mm
NT2: NetTie AGND-DGND; NetTie-2_SMD_Pad0.5mm
R1, R2, R3, R7: 10k 1%; R_0603_1608Metric
R4: 47 1%; R_0603_1608Metric
R5, R13: 100k 1%; R_0603_1608Metric
R6: 4.7k 1%; R_0603_1608Metric
R8, R9, R10: 2k 1%; R_0603_1608Metric
R11: 16k 1%; R_0603_1608Metric
R12: 100 1%; R_0603_1608Metric
R14, R15, R16, R17, R18, R19, R20, R21, R22, R23, R24, R25: 33 1%; R_0603_1608Metric
U1: 74AHCT1G125; SOT-23-5
U2: 74AHCT595D; SOIC-16_3.9x9.9mm_P1.27mm
U3: UCC27524DR; SOIC-8_3.9x4.9mm_P1.27mm
U4: OPA1678IDR; SOIC-8_3.9x4.9mm_P1.27mm
U5, U6: 74LVC2G34; SOT-363_SC-70-6

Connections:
+3V3: C11.1, C12.1, C13.1, C14.1, C15.1, C16.1, C17.1, C18.1, C19.1, C20.1, MK1.2, MK1.5, MK2.5, MK3.2, MK3.5, MK4.5, MK5.2, MK5.5, MK6.5, MK7.2, MK7.5, MK8.5, R2.2, U5.5, U6.5
+5V: C1.1, C3.1, U1.5, U2.16
+5VA: C6.1, U4.8
-5VA: C7.1, U4.4
AGND: C6.2, C7.2, C8.2, D2.1, D2.2, LS1.2, NT1.1, NT2.1, R5.2, R10.2, U4.5
DGND: C1.2, C3.2, C11.2, C12.2, C13.2, C14.2, C15.2, C16.2, C17.2, C18.2, C19.2, C20.2, MK1.3, MK2.2, MK2.3, MK3.3, MK4.2, MK4.3, MK5.3, MK6.2, MK6.3, MK7.3, MK8.2, MK8.3, NT2.2, R1.2, R3.2, R13.2, U1.1, U1.3, U2.8, U5.2, U6.2
DRV: D1.1, D1.2, R4.2
FB1: R7.2, R8.1, U4.2
INV2: C9.2, R11.1, U4.6
LIM: D2.3, R6.2, U4.3
MIC_CLK0: MK1.4, MK2.4, R14.2
MIC_CLK1: MK3.4, MK4.4, R15.2
MIC_CLK2: MK5.4, MK6.4, R16.2
MIC_CLK3: MK7.4, MK8.4, R17.2
MIC_CLK_IN: R13.1, U5.1, U5.3, U6.1, U6.3
MIC_DATA0: R18.2, R19.2
MIC_DATA1: R20.2, R21.2
MIC_DATA2: R22.2, R23.2
MIC_DATA3: R24.2, R25.2
N2: C9.1, C10.1, R9.2, R10.1
unnamed: R4.1, U3.7
unnamed: C8.1, R8.2
unnamed: R14.1, U5.6
unnamed: R15.1, U5.4
unnamed: R16.1, U6.6
unnamed: R17.1, U6.4
unnamed: MK1.1, R18.1
unnamed: MK2.1, R19.1
unnamed: MK3.1, R20.1
unnamed: MK4.1, R21.1
unnamed: MK5.1, R22.1
unnamed: MK6.1, R23.1
unnamed: MK7.1, R24.1
unnamed: MK8.1, R25.1
OUT2: C10.2, R11.2, R12.1, U4.7
PGND: C2.2, C4.2, C5.2, NT1.2, U3.3, U3.4
S1: R7.1, R9.1, U4.1
TX_BIT0: U2.15, U3.2
TX_CLR_N: R3.1, U2.10
TX_EN: U1.4, U3.1, U3.8
TX_EN_FPGA: R1.1, U1.2
TX_OE_N: R2.1, U2.13
VDRV: C2.1, C4.1, C5.1, U3.6
XD0: D1.3, LS1.1, R5.1, R6.1
